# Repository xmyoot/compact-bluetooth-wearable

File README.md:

# Compact Bluetooth Wearable

Rev A engineering prototype, KiCad 10.0.7. **Not released for fabrication.** Read `docs/design-review.md` for the current verification results and release blockers.

This independent portfolio project implements a wrist-worn BLE sensor: Raytac nRF52840 module, LIS3DH accelerometer, TMP117 skin-temperature sensor, protected single-cell Li-Po interface, BQ24074 power-path charging, USB-C charging/data, native USB bootloader support and SWD recovery. No wireless charging is included.

Open `hardware/Compact-Bluetooth-Wearable.kicad_pro` in KiCad 10. The schematic and PCB are editable native sources; project-local footprints are in `hardware/Wearable.pretty`.

- `docs/architecture.md`: circuit and mechanical assumptions, power budget, stack and charging behavior.
- `docs/bring-up.md`: electrical test sequence and recovery-header pinout.
- `docs/design-review.md`: actual ERC/DRC findings, analysis coverage and remaining blockers.
- `docs/client-request/`: original source photographs, retained as context rather than instructions.
- `analysis/`: machine reports, rejected routing candidates, BOM and reproduction scripts.
- `manufacturing/engineering-preview-NOT-FOR-FAB/`: review exports only; never send these to fabrication as a released package.
- `portfolio/`: renders and a draft case study; no prototype measurements have been fabricated or implied.

The optional buzzer is omitted. USB firmware is not yet implemented, and a blank nRF52840 requires initial SWD programming. A protected pack with a cell-mounted NTC and a qualified harness must be selected before connecting a battery.

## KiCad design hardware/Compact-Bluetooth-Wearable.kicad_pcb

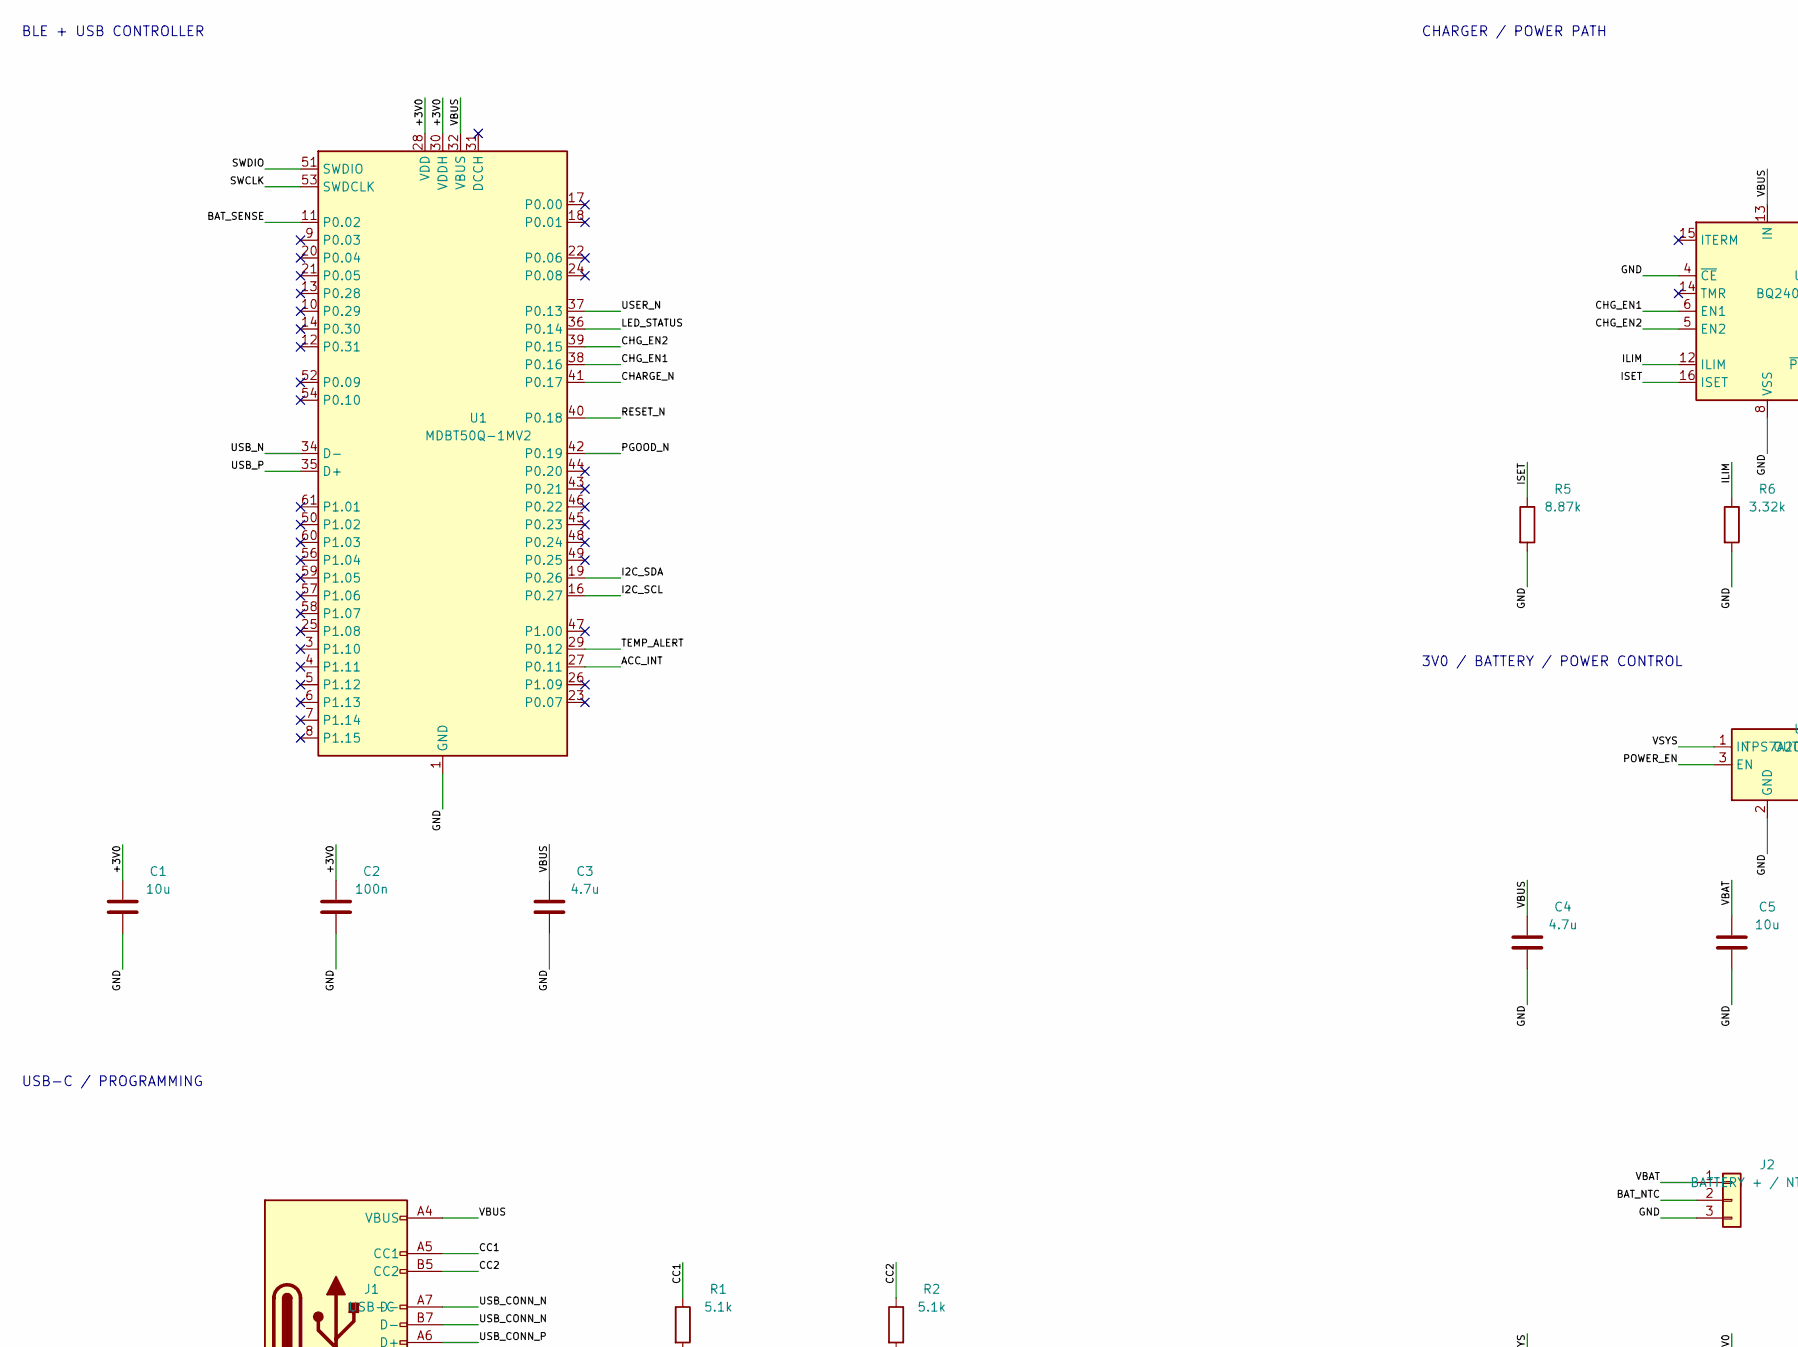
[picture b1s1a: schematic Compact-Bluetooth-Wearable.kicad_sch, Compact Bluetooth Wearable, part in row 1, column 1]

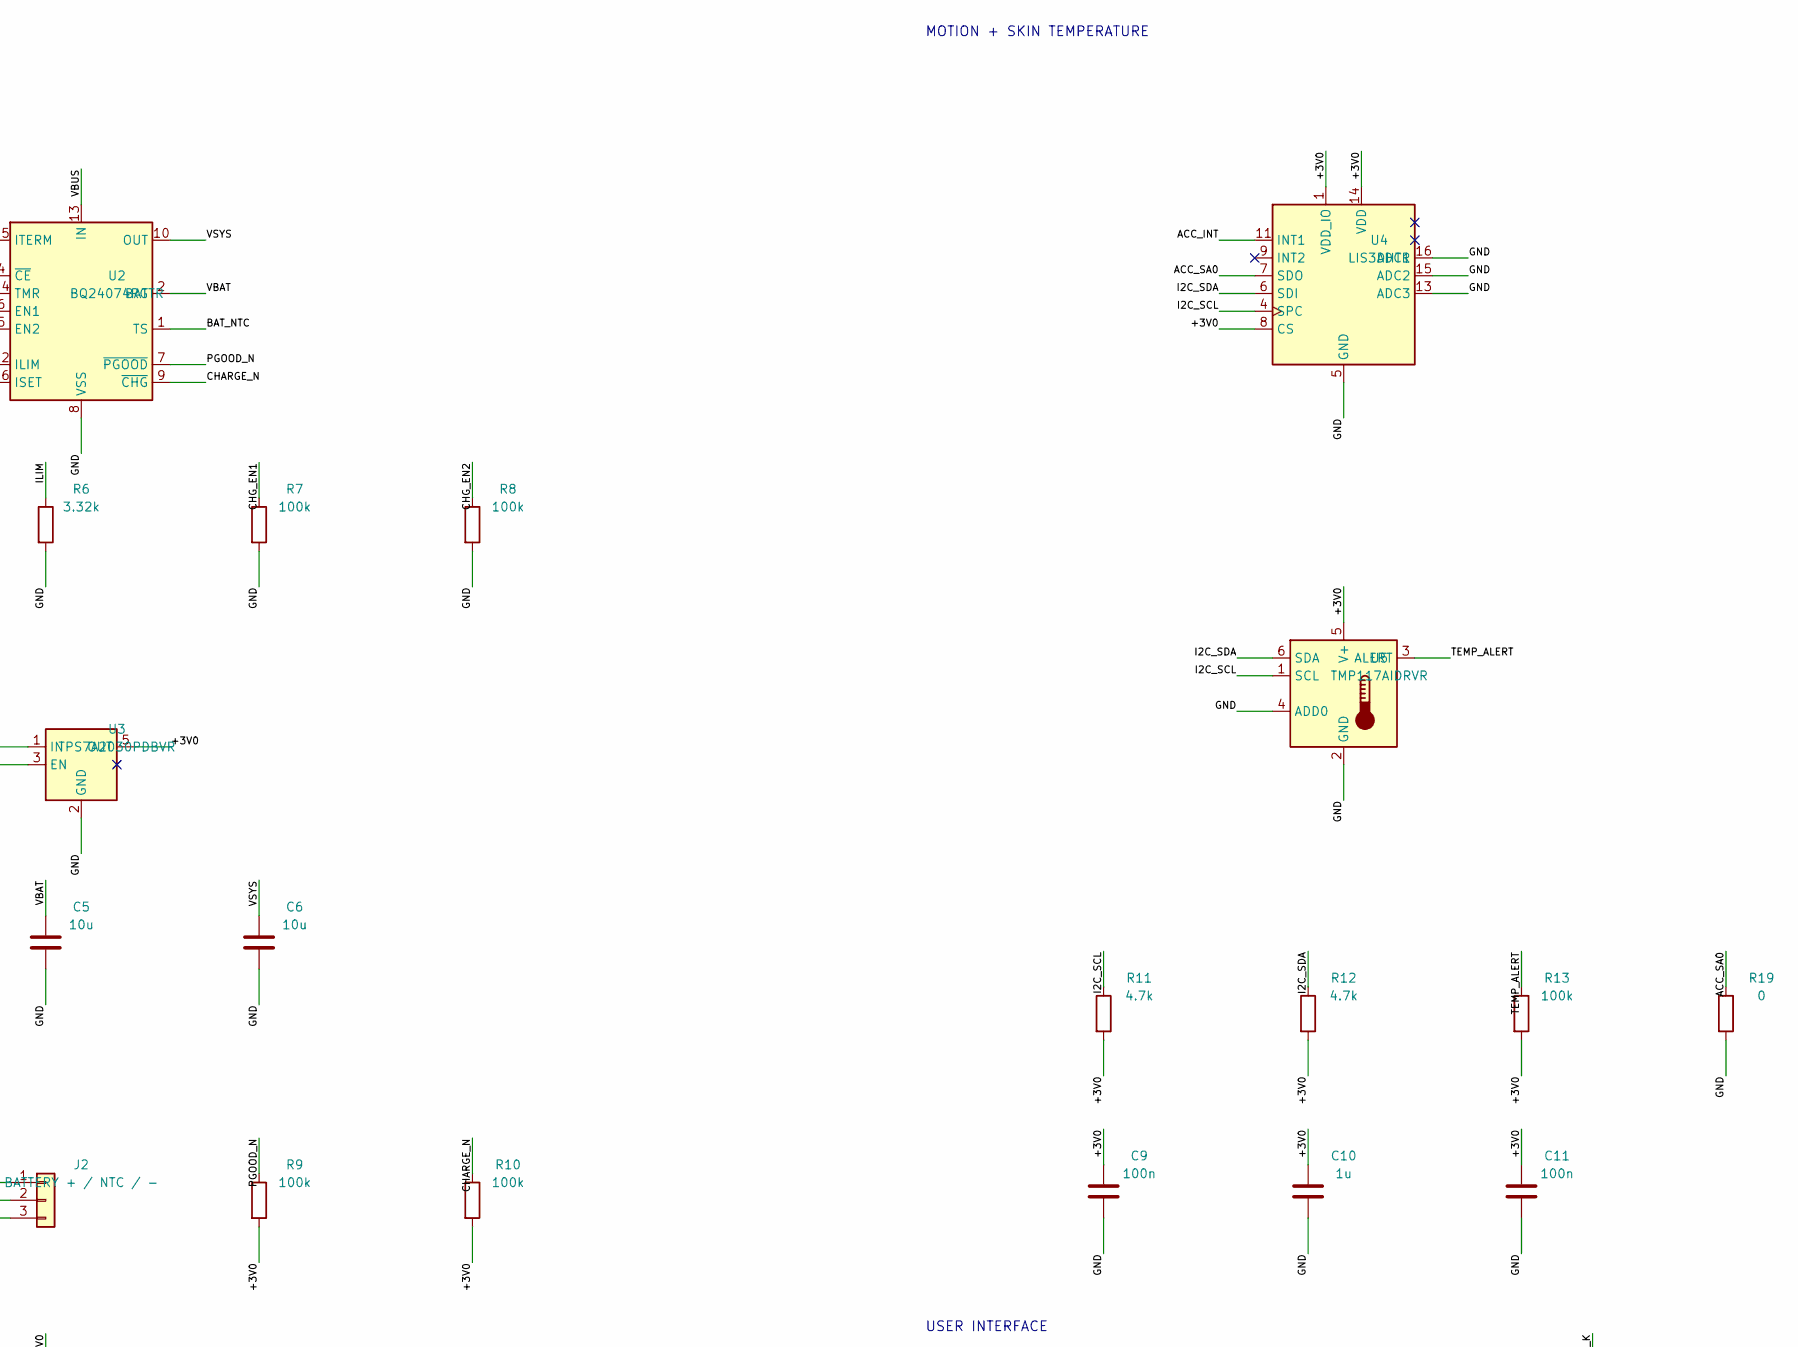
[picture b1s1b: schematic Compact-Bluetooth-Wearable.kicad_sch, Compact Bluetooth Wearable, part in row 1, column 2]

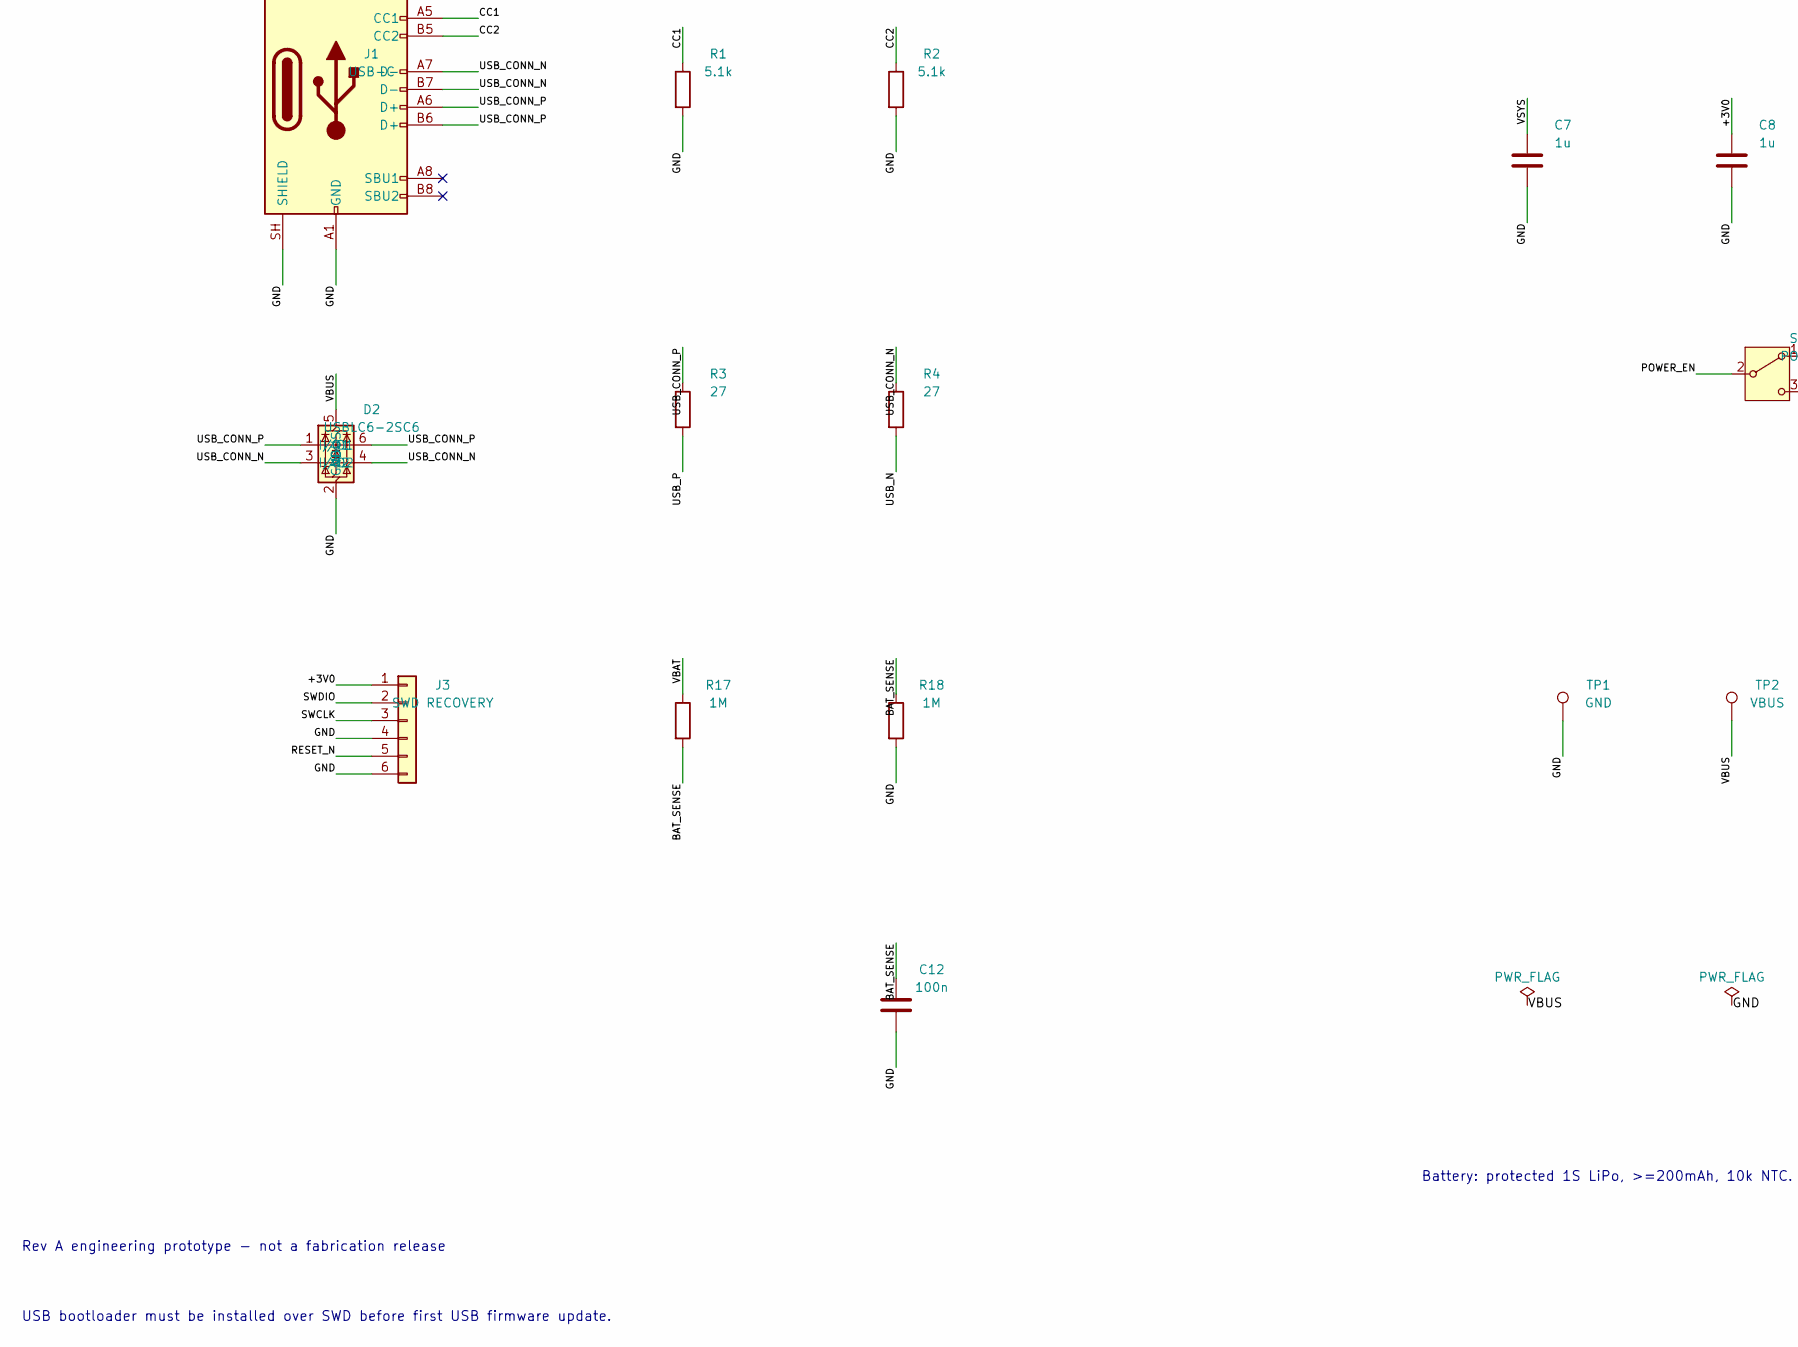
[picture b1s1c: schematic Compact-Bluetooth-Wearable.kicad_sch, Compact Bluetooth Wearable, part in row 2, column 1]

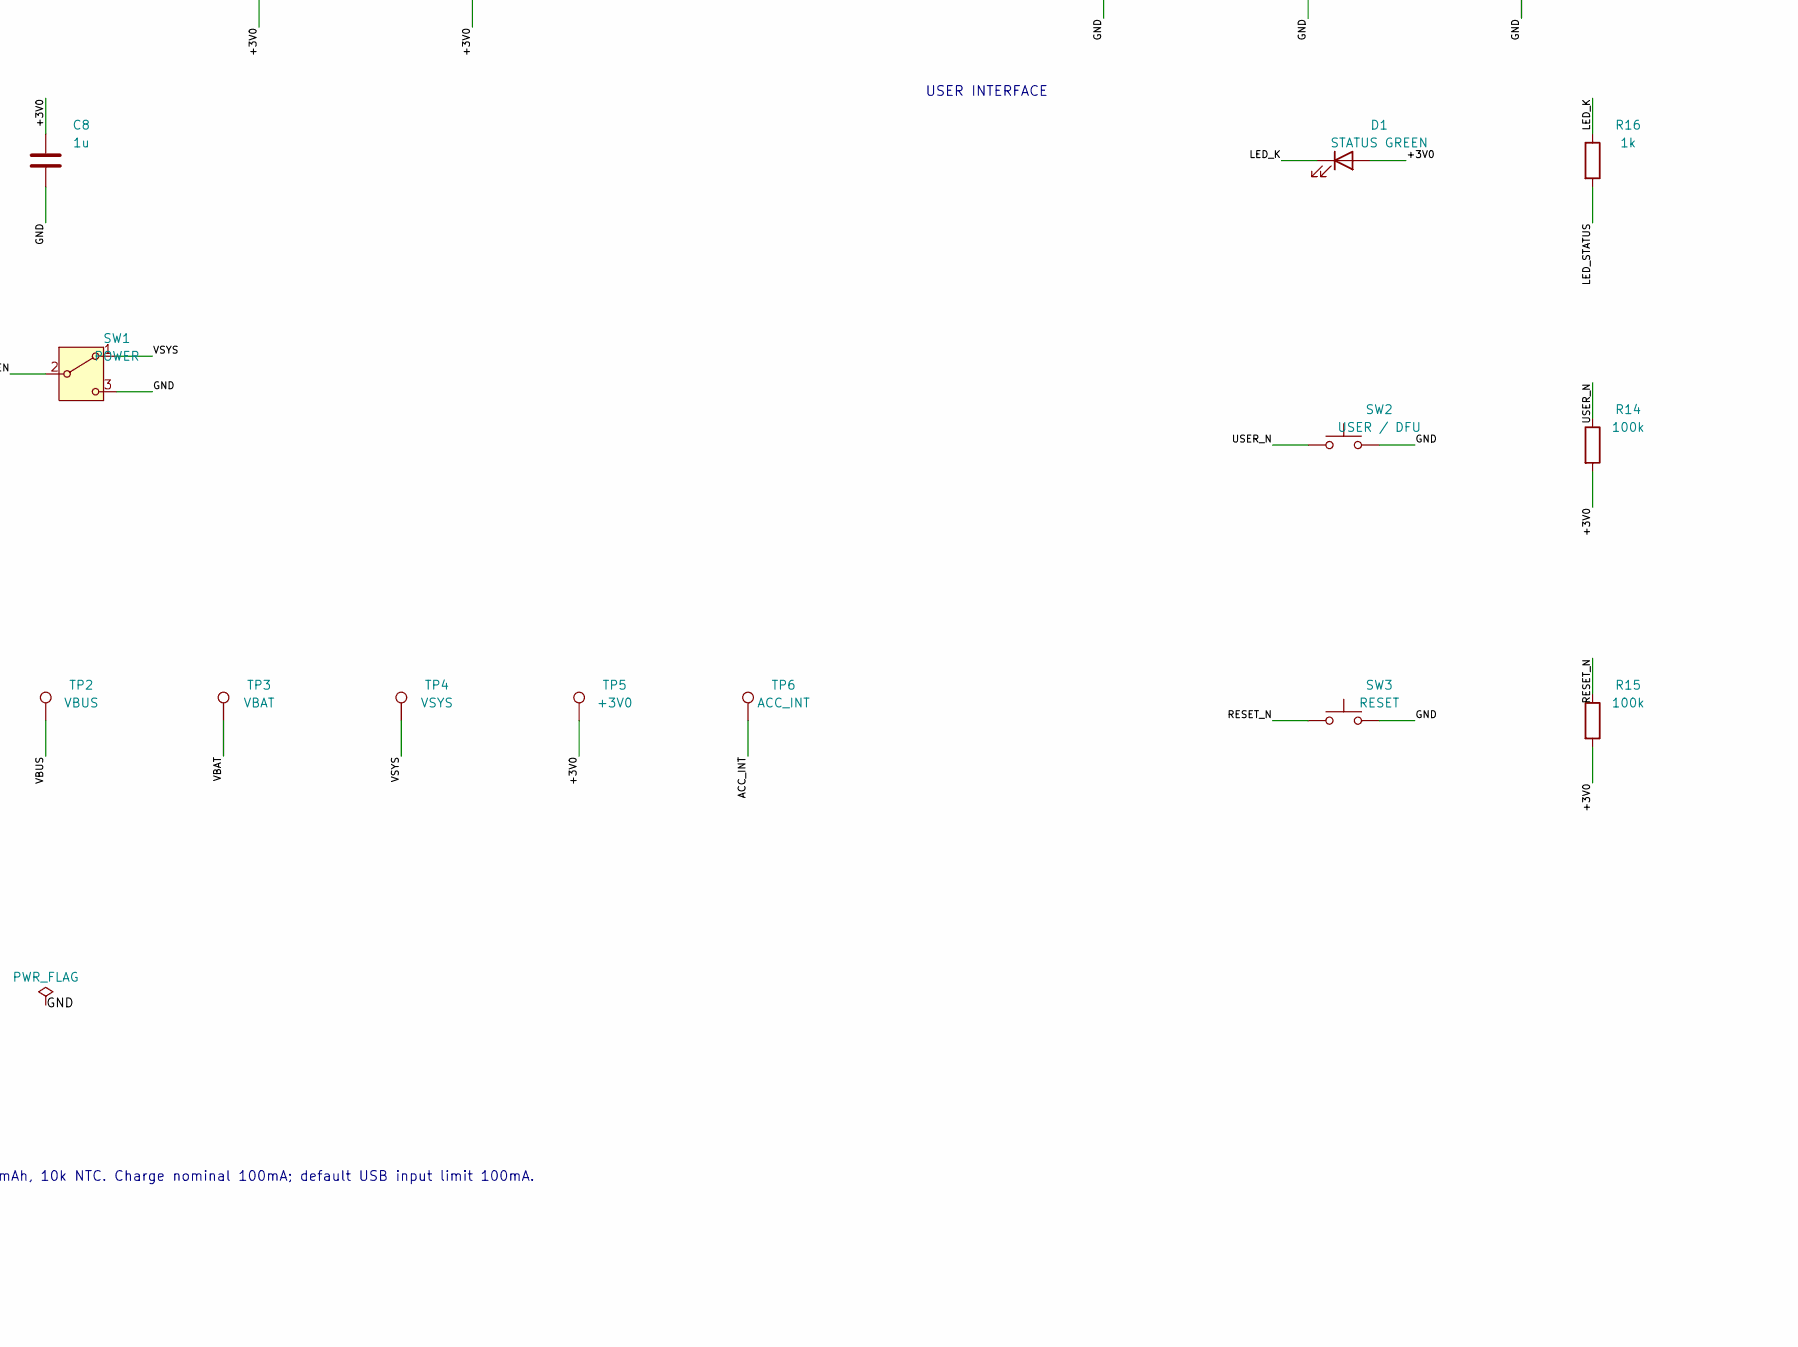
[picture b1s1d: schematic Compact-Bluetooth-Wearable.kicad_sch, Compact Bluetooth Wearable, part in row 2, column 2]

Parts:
C1, C5, C6: 10u; C_0603_1608Metric; MPN GRM188R60J106ME47D
C2, C9, C11, C12: 100n; C_0603_1608Metric; MPN GRM188R71C104KA01D
C3, C4: 4.7u; C_0603_1608Metric; MPN GRM188R60J475KE19D
C7, C8, C10: 1u; C_0603_1608Metric; MPN GRM188R61A105KA61D
D1: STATUS GREEN; LED_0603_1608Metric; MPN LTST-C190KGKT
D2: USBLC6-2SC6; SOT-23-6; MPN USBLC6-2SC6
J1: USB-C; USB_C_Receptacle_GCT_USB4105-xx-A_16P_TopMnt_Horizontal; MPN USB4105-GF-A
J2: BATTERY + / NTC / -; JST_PH_B3B-PH-K_1x03_P2.00mm_Vertical; MPN B3B-PH-K-S(LF)(SN)
J3: SWD RECOVERY; PinHeader_1x06_P1.27mm_Vertical; MPN 20021121-00006T4LF
R1, R2: 5.1k; R_0603_1608Metric; MPN RC0603FR-075K1L
R3, R4: 27; R_0603_1608Metric; MPN RC0603FR-0727RL
R5: 8.87k; R_0603_1608Metric; MPN RC0603FR-078K87L
R6: 3.32k; R_0603_1608Metric; MPN RC0603FR-073K32L
R7, R8, R9, R10, R13, R14, R15: 100k; R_0603_1608Metric; MPN RC0603FR-07100KL
R11, R12: 4.7k; R_0603_1608Metric; MPN RC0603FR-074K7L
R16: 1k; R_0603_1608Metric; MPN RC0603FR-071KL
R17, R18: 1M; R_0603_1608Metric; MPN RC0603FR-071ML
R19: 0; R_0603_1608Metric; MPN RC0603JR-070RL
SW1: POWER; SW_SPDT_PCM12; MPN PCM12SMTR
SW2: USER / DFU; SW_SPST_TL3342; MPN TL3342F160QG
SW3: RESET; SW_SPST_TL3342; MPN TL3342F160QG
TP1: GND; TestPoint_Pad_D1.0mm
TP2: VBUS; TestPoint_Pad_D1.0mm
TP3: VBAT; TestPoint_Pad_D1.0mm
TP4: VSYS; TestPoint_Pad_D1.0mm
TP5: +3V0; TestPoint_Pad_D1.0mm
TP6: ACC_INT; TestPoint_Pad_D1.0mm
U1: MDBT50Q-1MV2; Raytac_MDBT50Q; MPN MDBT50Q-1MV2
U2: BQ24074RGTR; VQFN-16-1EP_3x3mm_P0.5mm_EP1.6x1.6mm; MPN BQ24074RGTR
U3: TPS7A2030PDBVR; SOT-23-5; MPN TPS7A2030PDBVR
U4: LIS3DHTR; LGA-16_3x3mm_P0.5mm_LayoutBorder3x5y; MPN LIS3DHTR
U5: TMP117AIDRVR; TMP117_NoPasteEP; MPN TMP117AIDRVR

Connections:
/+3V0: C1.1, C2.1, C8.1, C9.1, C10.1, C11.1, D1.2 (A), J3.1, R9.2, R10.2, R11.2, R12.2, R13.2, R14.2, R15.2, TP5.1, U1.28 (VDD), U1.30 (VDDH), U3.5 (OUT), U4.1 (VDD_IO), U4.8 (CS), U4.14 (VDD), U5.5 (V+)
/ACC_INT: TP6.1, U1.27 (P0.11), U4.11 (INT1)
/ACC_SA0: R19.1, U4.7 (SDO)
/BAT_NTC: J2.2, U2.1 (TS)
/BAT_SENSE: C12.1, R17.2, R18.1, U1.11 (P0.02)
/CC1: J1.A5 (CC1), R1.1
/CC2: J1.B5 (CC2), R2.1
/CHARGE_N: R10.1, U1.41 (P0.17), U2.9 (~CHG)
/CHG_EN1: R7.1, U1.38 (P0.16), U2.6 (EN1)
/CHG_EN2: R8.1, U1.39 (P0.15), U2.5 (EN2)
/GND: C1.2, C2.2, C3.2, C4.2, C5.2, C6.2, C7.2, C8.2, C9.2, C10.2, C11.2, C12.2, D2.2 (GND), J1.A1 (GND), J1.A12 (GND), J1.B1 (GND), J1.B12 (GND), J1.SH (SHIELD), J2.3, J3.4, J3.6, R1.2, R2.2, R5.2, R6.2, R7.2, R8.2, R18.2, R19.2, SW1.3 (C), SW2.2, SW3.2, TP1.1, U1.1 (GND), U1.2 (GND), U1.15 (GND), U1.33 (GND), U1.55 (GND), U2.4 (~CE), U2.8 (VSS), U2.17 (VSS), U3.2 (GND), U4.5 (GND), U4.10 (GND), U4.12 (GND), U4.13 (ADC3), U4.15 (ADC2), U4.16 (ADC1), U5.2 (GND), U5.4 (ADD0)
/I2C_SCL: R11.1, U1.16 (P0.27), U4.4 (SPC), U5.1 (SCL)
/I2C_SDA: R12.1, U1.19 (P0.26), U4.6 (SDI), U5.6 (SDA)
/ILIM: R6.1, U2.12 (ILIM)
/ISET: R5.1, U2.16 (ISET)
/LED_K: D1.1 (K), R16.1
/LED_STATUS: R16.2, U1.36 (P0.14)
/PGOOD_N: R9.1, U1.42 (P0.19), U2.7 (~PGOOD)
/POWER_EN: SW1.2 (B), U3.3 (EN)
/RESET_N: J3.5, R15.1, SW3.1, U1.40 (P0.18)
/SWCLK: J3.3, U1.53 (SWDCLK)
/SWDIO: J3.2, U1.51 (SWDIO)
/TEMP_ALERT: R13.1, U1.29 (P0.12), U5.3 (ALERT)
/USB_CONN_N: D2.3 (I/O2), D2.4 (I/O2), J1.A7 (D-), J1.B7 (D-), R4.1
/USB_CONN_P: D2.1 (I/O1), D2.6 (I/O1), J1.A6 (D+), J1.B6 (D+), R3.1
/USB_N: R4.2, U1.34 (D-)
/USB_P: R3.2, U1.35 (D+)
/USER_N: R14.1, SW2.1, U1.37 (P0.13)
/VBAT: C5.1, J2.1, R17.1, TP3.1, U2.2 (BAT), U2.3 (BAT)
/VBUS: C3.1, C4.1, D2.5 (VBUS), J1.A4 (VBUS), J1.A9 (VBUS), J1.B4 (VBUS), J1.B9 (VBUS), TP2.1, U1.32 (VBUS), U2.13 (IN)
/VSYS: C6.1, C7.1, SW1.1 (A), TP4.1, U2.10 (OUT), U2.11 (OUT), U3.1 (IN)

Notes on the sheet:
BLE + USB CONTROLLER
USB-C / PROGRAMMING
CHARGER / POWER PATH
3V0 / BATTERY / POWER CONTROL
MOTION + SKIN TEMPERATURE
USER INTERFACE
Rev A engineering prototype - not a fabrication release
USB bootloader must be installed over SWD before first USB firmware update.
Battery: protected 1S LiPo, >=200mAh, 10k NTC. Charge nominal 100mA; default USB input limit 100mA.

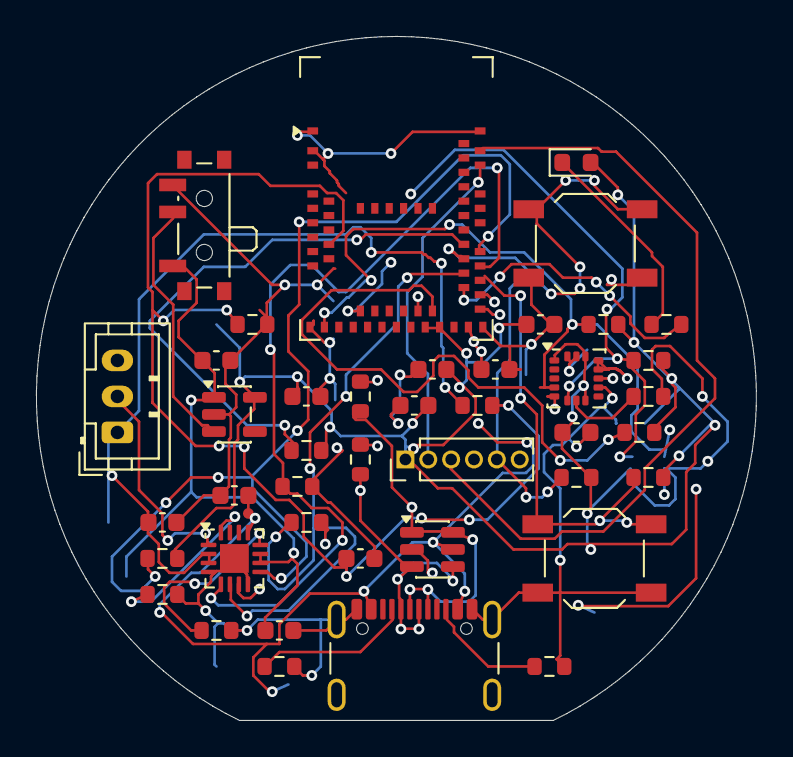
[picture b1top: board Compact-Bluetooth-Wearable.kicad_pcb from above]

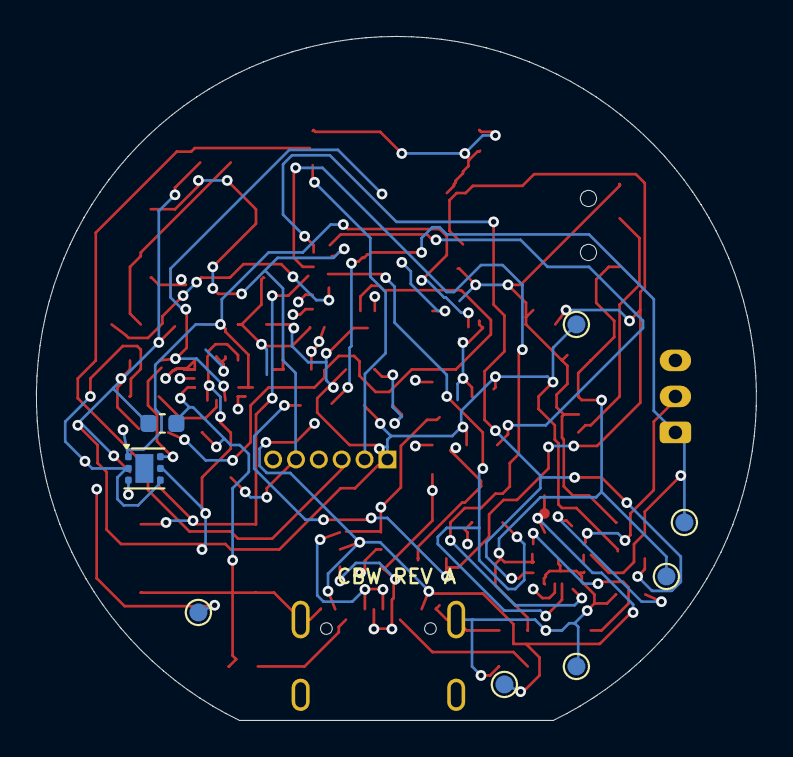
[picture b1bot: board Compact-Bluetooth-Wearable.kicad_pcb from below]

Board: 4 copper layers, 40.0 x 38.0 mm, 50 parts (8 on the bottom side), 31 nets.

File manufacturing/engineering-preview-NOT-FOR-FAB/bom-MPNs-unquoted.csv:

Reference,Qty,Value,Footprint,MPN,Manufacturer,Chosen_Distributor,Datasheet,Validated,DNP,Notes
"C1,C5,C6",3,10u,0603,GRM188R60J106ME47D,Murata,,,,,
"C2,C9,C11,C12",4,100n,0603,GRM188R71C104KA01D,Murata,,,,,
"C3,C4",2,4.7u,0603,GRM188R60J475KE19D,Murata,,,,,
"C7,C8,C10",3,1u,0603,GRM188R61A105KA61D,Murata,,,,,
D1,1,STATUS GREEN,0603,LTST-C190KGKT,Lite-On,,,,,
D2,1,USBLC6-2SC6,SOT-23-6,USBLC6-2SC6,STMicroelectronics,,https://www.st.com/resource/en/datasheet/usblc6-2.pdf,,,
J1,1,USB-C,USB_C_Receptacle_GCT_USB4105-xx-A_16P_TopMnt_Horizontal,USB4105-GF-A,GCT,,https://gct.co/files/drawings/usb4105.pdf,,,
J2,1,BATTERY + / NTC / -,JST_PH_B3B-PH-K_1x03_P2.00mm_Vertical,B3B-PH-K-S(LF)(SN),JST,,,,,"Use protected 1S 4.2V LiPo >=200mAh, 10k NTC at cell; verify mating harness polarity. Pack MPN not released."
J3,1,SWD RECOVERY,PinHeader_1x06_P1.27mm_Vertical,20021121-00006T4LF,Amphenol,,,,,"Optional populated header; debugger must sense target voltage, not power target."
"R1,R2",2,5.1k,0603,RC0603FR-075K1L,Yageo,,,,,
"R3,R4",2,27,0603,RC0603FR-0727RL,Yageo,,,,,
R5,1,8.87k,0603,RC0603FR-078K87L,Yageo,,,,,
R6,1,3.32k,0603,RC0603FR-073K32L,Yageo,,,,,
"R7,R8,R9,R10,R13,R14,R15",7,100k,0603,RC0603FR-07100KL,Yageo,,,,,
"R11,R12",2,4.7k,0603,RC0603FR-074K7L,Yageo,,,,,
R16,1,1k,0603,RC0603FR-071KL,Yageo,,,,,
"R17,R18",2,1M,0603,RC0603FR-071ML,Yageo,,,,,
R19,1,0,0603,RC0603JR-070RL,Yageo,,,,,
SW1,1,POWER,SW_SPDT_PCM12,PCM12SMTR,C&K,,,,,
SW2,1,USER / DFU,SW_SPST_TL3342,TL3342F160QG,E-Switch,,,,,
SW3,1,RESET,SW_SPST_TL3342,TL3342F160QG,E-Switch,,,,,
U1,1,MDBT50Q-1MV2,Raytac_MDBT50Q,MDBT50Q-1MV2,Raytac,,https://www.raytac.com/download/index.php?index_id=43,,,
U2,1,BQ24074RGTR,VQFN-16-1EP_3x3mm_P0.5mm_EP1.6x1.6mm,BQ24074RGTR,Texas Instruments,,https://www.ti.com/lit/ds/symlink/bq24074.pdf,,,TMR floating: default timer. ITERM floating: 10% termination. Battery requires external protection and 10k NTC.
U3,1,TPS7A2030PDBVR,SOT-23-5,TPS7A2030PDBVR,Texas Instruments,,https://www.ti.com/lit/ds/symlink/tps7a20.pdf,,,
U4,1,LIS3DHTR,LGA-16_3x3mm_P0.5mm_LayoutBorder3x5y,LIS3DHTR,STMicroelectronics,,https://www.st.com/resource/en/datasheet/cd00274221.pdf,,,
U5,1,TMP117AIDRVR,TMP117_NoPasteEP,TMP117AIDRVR,Texas Instruments,,https://www.ti.com/lit/ds/symlink/tmp117.pdf,,,Exposed pad unsoldered: no paste aperture. Skin-facing package; enclosure thermal contact requires validation.
